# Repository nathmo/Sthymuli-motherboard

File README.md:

# Sthymuli-motherboard
This repo contains the PCB for the Sthymuli motherboard. Sthymuli is an educative robot aimed at children whith the aim of promoting collaborative learning.

The motherboard is designed arround a doughnut shape with addons that plug in the center. the shape was chosen to encourage equal access to up to four children at a time interracting with the device.

the circuit is splitted between one motherboard and three cardinalboard 
this repo has the motherboard

the cardinal board can be found there : https://github.com/nathmo/Sthymuli-cardinalboard

# Feature
The device contains the following sensors 

===

* # USB-C connector
* # Batterie + BMS
* # ESP32 + STM32
* # Speaker
* # Microphone
* # capacitive buttons (distributed arround the doughnut as discussed last time)
* # IR remote receive
* # 4 IR proximity Sensor
* # Motor Driver (so they can just connect the two wire of the motor and dont need to add a Hbridge on the dauther board
* # RGB LED (there I need to count how many and decide with you what we keep and what we breakout for the daugther board

# Daugther boards

the following will be available for the daugther board :

* IMU
* color sensor
* 2 DC motor channel
* LEDs
* IR proximity sensor / analog pin that can be used for sensing

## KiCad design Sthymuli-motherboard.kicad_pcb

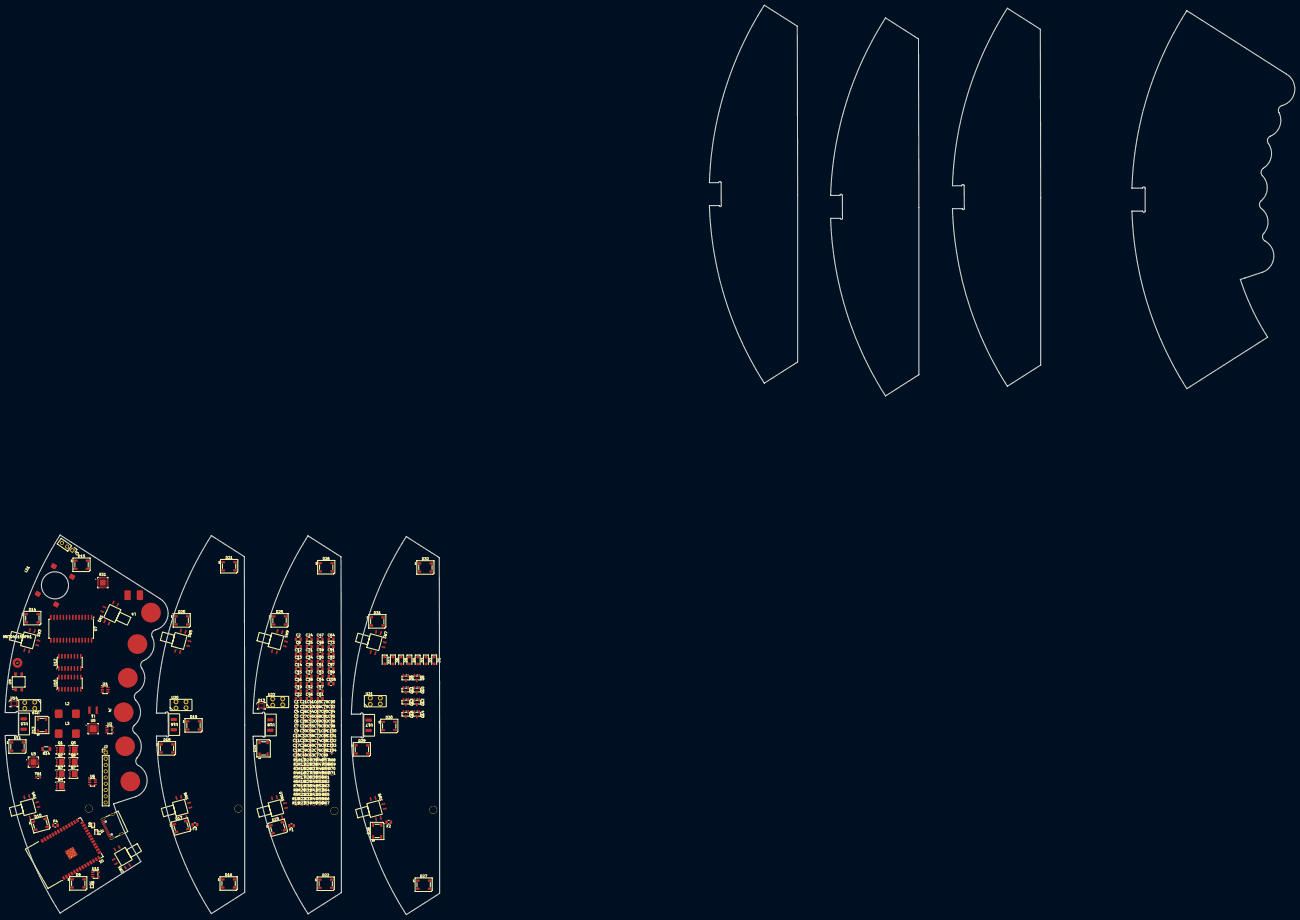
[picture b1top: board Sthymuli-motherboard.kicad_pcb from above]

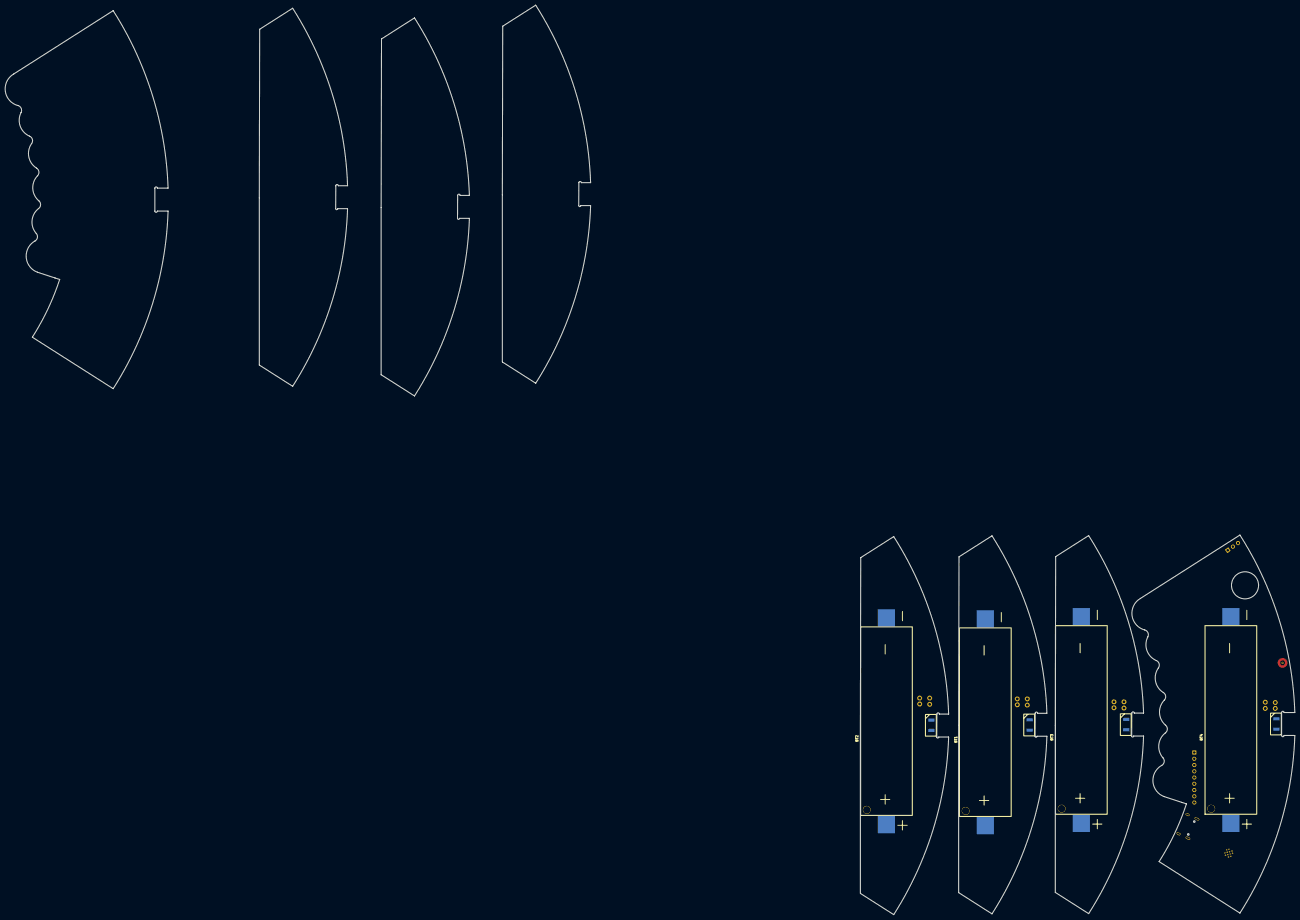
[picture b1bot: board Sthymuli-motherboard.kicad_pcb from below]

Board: 2 copper layers, 524.0 x 369.5 mm, 275 parts (4 on the bottom side), 189 nets, no tracks yet.

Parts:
BT1, BT2, BT3, BT4: Battery_Cell; Battery_Holder_18650_robop
C1, C10, C23, C32, C36, C43, C45, C55, C56, C62, C63, C65, C67, C68, C70, C71, C72, C74, C75, C76, C77, C78, C79, C80, C81, C82, C83, C84, C85, C86, C87, C88, C89, C90, C92, C94, C95, C96, C98, C100, C101, C102, C103, C104: 100nF; C_0402_1005Metric
C2: 22 uF; C_0805_2012Metric
C3, C4, C5, C6, C7: 220nF; C_0402_1005Metric
C8, C12, C13, C47, C48, C57, C61, C91, C93, C97, C99: 1uF; C_0805_2012Metric
C9, C11, C39, C40, C41, C44: 100pF; C_0402_1005Metric
C14, C15, C16, C19, C31, C34, C35, C64, C73, C105: 10uF; C_0805_2012Metric
C17: 1.8nF; C_0402_1005Metric
C18: 470nF; C_0402_1005Metric
C20: 33pF; C_0402_1005Metric
C21: 15pF; C_0402_1005Metric
C22: 680pF; C_0805_2012Metric
C24, C25: 33nF; C_0805_2012Metric
C26: 10nF; C_0402_1005Metric
C27, C28, C29: 10uF; C_0402_1005Metric
C30, C33: 47nF; C_0402_1005Metric
C37, C38, C46, C49: 22uF; C_0805_2012Metric
C42: 2.2uF; C_0805_2012Metric
C50, C54: 10nF; C_0805_2012Metric
C51: 1.5nF; C_0805_2012Metric
C52: 330pF; C_0402_1005Metric
C53: 4.7uF; C_0805_2012Metric
C58, C60: 1nF; C_0402_1005Metric
C59: 1uF; C_0402_1005Metric
C66, C69: 20pF; C_0402_1005Metric
D1, D2, D3, D4: D_Schottky; D_SOD-123F
D5, D6, D12: D; D_SOD-123F
D7, D8: LESD5D5.0C11G; D_SOD-523
D9, D10, D11, D13, D14, D15, D16, D17, D18, D19, D20, D21, D22, D23, D24, D25, D26, D27, D28, D29, D30, D31, D32: WS2812B; LED_WS2812B_PLCC4_5.0x5.0mm_P3.2mm
ES1: ES8374; QFN-28-1EP_4x4mm_P0.45mm_EP2.4x2.4mm
F1, F2, F3, F4: Fuse; R_0805_2012Metric
J1: USB_C_Receptacle_USB2.0_16P; USB_C_Receptacle_G-Switch_GT-USB-7010ASV
J2: Conn_01x09; PinHeader_1x09_P2.54mm_Vertical
J3: Conn_01x03; PinHeader_1x03_P2.54mm_Vertical
J4: Conn_01x06; ConnectorSpring
L1: 2.2uH; FHD4020S-2R2MT
L2, L3: 3.3uH; FXL0630-3R3-M
L4: L; TDK VFS5045VA301
LS1: Speaker; Speaker KELIKING KLJ-01304T-08R07W
MKTD4015BPN1: Microphone; SAMZO MIC-4013-G-G00
Q1, Q2, Q3, Q4, Q5, Q6: Q_NMOS_Depletion_GSD; VSON-8_3.3x3.3mm_P0.65mm_NexFET
Q7: PMOS; VSON-8_3.3x3.3mm_P0.65mm_NexFET
Q8, Q9, Q10, Q11, Q12, Q13, Q14, Q15: NX7002AK; SOT-23
R1, R2, R3, R4, R6, R9, R15, R36, R37: 10R; C_0201_0603Metric
R5, R7: 5K1; C_0201_0603Metric
R8, R13, R16, R48, R59, R69, R70: 100R; C_0201_0603Metric
R10, R12: OL; C_0201_0603Metric
R11, R68: 0R; C_0201_0603Metric
R14: 0.001 R; R_1206_3216Metric
R17: 100K; C_0201_0603Metric
R18: 300K; C_0201_0603Metric
R19, R26: 10M; C_0201_0603Metric
R20: 470K; C_0201_0603Metric
R21: 270K; C_0201_0603Metric
R22, R23, R49, R58: 2K2; C_0201_0603Metric
R24, R28: 5k1; C_0201_0603Metric
R25: 40.2K; C_0201_0603Metric
R27: 1R; C_0201_0603Metric
R29, R31: 4.99R; C_0201_0603Metric
R30, R43: 0.01 R; C_0201_0603Metric
R32, R33, R34, R42, R45, R46, R47, R71: 10K; C_0201_0603Metric
R35: 30K; C_0201_0603Metric
R38: 47K; C_0201_0603Metric
R39: 15K; C_0201_0603Metric
R40: 137K; C_0201_0603Metric
R41: 53.6K; C_0201_0603Metric
R44: 1K; C_0201_0603Metric
R50, R51, R52, R53, R54, R55, R56, R57: 3K3; C_0201_0603Metric
R60, R61, R62, R63, R64, R65, R66, R67: 27R; C_0201_0603Metric
SW1, SW2, SW3, SW4, SW5, SW6, SW7, SW8, SW9, SW10: SW_Push; XKB5858
TH1: Thermistor; R_0603_1608Metric
U1: ESP32-S3-WROOM-1
U2: AP2112K-3.3; SOT-23-5
U3: BQ76905RGRR; Texas_RGP0020H_VQFN-20-1EP_4x4mm_P0.5mm_EP2.4x2.4mm
U4, U6: AP62300WU; TSOT-23-6
U5: BQ25713; QFN-32-1EP_4x4mm_P0.4mm_EP2.9x2.9mm
U7: MCP23017_SO; SOIC-28W_7.5x17.9mm_P1.27mm
U8: AP22913CN4; WLCSP-4_0.89x0.89mm_Layout2x2_P0.5mm
U9: IRM-H6xxT; Everlight_IRM-H6xxT
U10, U12: 74HC4051; SOIC-16_3.9x9.9mm_P1.27mm
U11: MCP6L01x-xOT; SOT-23-5
U13, U14: LSM6DS3; LGA-14_3x2.5mm_P0.5mm_LayoutBorder3x4y
U15, U16, U17, U18: ITR9909; ITR_9909_Horizontal
U19, U20, U21, U22: ITR9909; ITR_9909_Vertical

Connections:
+3V3: C47.2, C50.2, C54.2, C55.1, C56.1, C64.1, C67.1, C103.2, C105.2, ES1.5 (PVDD), ES1.6 (DVDD), ES1.16 (AVDD), J2.1, L4.1, R22.2, R23.2, R33.2, R34.1, R45.1, R48.2, R50.1, R51.1, R52.1, R53.1, R54.1, R55.1, R56.1, R57.1, R60.2, R61.2, R62.2, R63.2, R64.2, R65.2, R66.2, R67.2, R71.2, U2.5 (VOUT), U7.9 (VDD), U7.18 (~RESET), U8.A1 (OUT), U10.16 (VCC), U11.5 (V+), U12.16 (VCC), U13.1 (SDO/SA0), U13.5 (VDDIO), U13.8 (VDD), U13.12 (CS), U14.5 (VDDIO), U14.8 (VDD), U14.12 (CS)
+5V: C44.2, C46.2, C49.2, C62.1, C63.1, C68.1, C70.1, C71.1, C72.1, C74.1, C76.1, C77.1, C78.1, C79.1, C80.1, C81.1, C82.1, C83.1, C84.1, C85.1, C86.1, C87.1, C88.1, C89.1, C90.1, C92.1, C94.1, C95.1, C96.1, C98.1, C100.1, C101.1, C102.1, C104.1, D9.1 (VDD), D10.1 (VDD), D11.1 (VDD), D12.2 (A), D14.1 (VDD), D15.1 (VDD), D16.1 (VDD), D17.1 (VDD), D18.1 (VDD), D19.1 (VDD), D20.1 (VDD), D21.1 (VDD), D22.1 (VDD), D23.1 (VDD), D24.1 (VDD), D25.1 (VDD), D26.1 (VDD), D27.1 (VDD), D28.1 (VDD), D29.1 (VDD), D30.1 (VDD), D31.1 (VDD), D32.1 (VDD), J4.1, L3.2, R10.1, R41.1
+BATT: BT1.1 (+), C45.1, D5.2 (A), D6.2 (A), F1.1, R1.1, R37.1, R43.2
/D+: D8.1 (K), J1.A6 (D+), J1.B6 (D+), U1.14 (USB_D+)
/D-: D7.1 (K), J1.A7 (D-), J1.B7 (D-), U1.13 (USB_D-)
/MICBIAS: C99.1, ES1.21 (MICBIAS), R59.2
/MIC_N: C59.1, ES1.23 (LIN2)
/MIC_P: C57.1, ES1.22 (RIN2)
ACC_A_INT1: U1.11 (IO18), U14.4 (INT1)
ACC_B_INT1: U1.10 (IO17), U13.4 (INT1)
BMS_ALERT: U1.15 (IO3), U3.14 (ALERT)
BOOT_MODE: C32.1, SW2.2, U1.27 (IO0)
CHRG_OK: R34.2, U5.4 (CHRG_OK), U7.24 (GPA3)
EXT_GPIO_1: J4.4, U1.7 (IO7)
EXT_GPIO_2: J4.5, U1.12 (IO8)
GND: C1.2, C2.2, C4.1, C7.1, C8.2, C11.2, C12.2, C13.2, C14.2, C15.2, C16.2, C17.2, C18.2, C19.2, C20.2, C21.2, C22.2, C23.2, C24.2, C25.2, C26.2, C27.2, C28.2, C29.2, C31.2, C32.2, C34.2, C35.2, C37.1, C38.1, C40.2, C41.2, C42.1, C46.1, C47.1, C48.1, C49.1, C50.1, C53.2, C54.1, C55.2, C56.2, C58.2, C60.2, C61.2, C62.2, C63.2, C65.2, C66.2, C68.2, C69.2, C70.2, C71.2, C72.2, C74.2, C76.2, C77.2, C78.2, C79.2, C80.2, C81.2, C82.2, C83.2, C84.2, C85.2, C86.2, C87.2, C88.2, C89.2, C90.2, C92.2, C94.2, C95.2, C96.2, C98.2, C100.2, C101.2, C102.2, C104.2, D7.2 (A), D8.2 (A), D9.3 (VSS), D10.3 (VSS), D11.3 (VSS), D13.3 (VSS), D14.3 (VSS), D15.3 (VSS), D16.3 (VSS), D17.3 (VSS), D18.3 (VSS), D19.3 (VSS), D20.3 (VSS), D21.3 (VSS), D22.3 (VSS), D23.3 (VSS), D24.3 (VSS), D25.3 (VSS), D26.3 (VSS), D27.3 (VSS), D28.3 (VSS), D29.3 (VSS), D30.3 (VSS), D31.3 (VSS), D32.3 (VSS), J1.A1 (GND), J1.A12 (GND), J1.B1 (GND), J1.B12 (GND), J1.S1 (SHIELD), J2.9, J4.6, Q2.2 (S), Q4.2 (S), Q5.2 (S), Q8.2 (S), Q9.2 (S), Q10.2 (S), Q11.2 (S), Q12.2 (S), Q13.2 (S), Q14.2 (S), Q15.2 (S), R5.1, R7.1, R18.2, R21.2, R26.2, R35.2, R39.2, R40.2, R42.2, R46.2, R49.1, R68.1, SW1.1, SW2.1, SW3.2, SW4.2, SW5.2, SW6.2, SW7.2, SW8.2, SW9.2, SW10.2, TH1.2, U1.1 (GND), U1.40 (GND), U1.41 (GND), U2.2 (GND), U3.11 (VSS), U3.21 (EXP), U4.1 (GND), U5.27 (PGND), U6.1 (GND), U7.10 (VSS), U7.15 (A0), U7.16 (A1), U7.17 (A2), U8.B1 (GND), U9.1 (GND), U9.2 (GND), U10.6 (~E), U10.7 (VEE), U10.8 (GND), U11.2 (V-), U12.6 (~E), U12.7 (VEE), U12.8 (GND), U13.2 (SDX), U13.3 (SCX), U13.6 (GND), U13.7 (GND), U14.1 (SDO/SA0), U14.2 (SDX), U14.3 (SCX), U14.6 (GND), U14.7 (GND), U15.3, U16.3, U17.3, U18.3, U19.3, U20.3, U21.3, U22.3
GNDA: C64.2, C67.2, C73.2, C75.2, C91.2, C93.2, C97.2, C99.2, C103.1, C105.1, ES1.3 (DGND), ES1.12 (SPKGND), ES1.17 (AGND), ES1.29 (PGND), R68.2
GPIO_INTA: U1.38 (IO2), U7.20 (INTA)
GPIO_INTB: U1.39 (IO1), U7.19 (INTB)
I2S_DOUT: ES1.8 (ASDOUT), U1.8 (IO15)
I2S_DSIN: ES1.10 (ASDIN), U1.22 (IO14)
I2S_LCLK: ES1.9 (DLRCK), U1.21 (IO13)
I2S_MCLK: ES1.2 (MCLK), U1.9 (IO16)
I2S_SCLK: ES1.7 (BCLK), U1.20 (IO12)
INT_WS2812_DIN: D13.4 (DIN), U1.17 (IO9)
IR_MODULATION: U1.18 (IO10), U12.3 (A)
IR_REC_0: R50.2, U10.13 (A0), U15.4
IR_REC_1: R51.2, U10.14 (A1), U16.4
IR_REC_2: R52.2, U10.15 (A2), U17.4
IR_REC_3: R53.2, U10.12 (A3), U18.4
IR_REC_4: R54.2, U10.1 (A4), U19.4
IR_REC_5: R55.2, U10.5 (A5), U20.4
IR_REC_6: R56.2, U10.2 (A6), U21.4
IR_REC_7: R57.2, U10.4 (A7), U22.4
IR_S0: U7.26 (GPA5), U10.11 (S0), U12.11 (S0)
IR_S1: U7.27 (GPA6), U10.10 (S1), U12.10 (S1)
IR_S2: U7.28 (GPA7), U10.9 (S2), U12.9 (S2)
IR_TRA_0: Q8.1 (G), U12.13 (A0)
IR_TRA_1: Q9.1 (G), U12.14 (A1)
IR_TRA_2: Q10.1 (G), U12.15 (A2)
IR_TRA_3: Q11.1 (G), U12.12 (A3)
IR_TRA_4: Q12.1 (G), U12.1 (A4)
IR_TRA_5: Q13.1 (G), U12.5 (A5)
IR_TRA_6: Q14.1 (G), U12.2 (A6)
IR_TRA_7: Q15.1 (G), U12.4 (A7)
IR_analog: C52.1, R47.1, U1.4 (IO4), U11.1
IR_receiver: U1.19 (IO11), U9.3 (OUT)
unnamed: BT1.2 (-), BT2.1 (+), D1.2 (A), F2.1, R2.1
unnamed: BT2.2 (-), BT3.1 (+), D2.2 (A), F3.1, R3.1
unnamed: BT3.2 (-), BT4.1 (+), D3.2 (A), F4.1, R4.1
unnamed: BT4.2 (-), D4.2 (A), R6.1, R13.2, R14.2
unnamed: C14.1, C15.1, C16.1, C19.1, R11.1, R27.2, R29.2, R30.2
unnamed: C17.1, R25.2
unnamed: C22.1, R32.2
unnamed: C51.2, R44.1
unnamed: C61.1, R58.1, R59.1
unnamed: D1.1 (K), F1.2
unnamed: D2.1 (K), F2.2
unnamed: D3.1 (K), F3.2
unnamed: D4.1 (K), F4.2
unnamed: D5.1 (K), R8.1
unnamed: D6.1 (K), R9.1
unnamed: D10.2 (DOUT), D15.4 (DIN)
unnamed: D11.2 (DOUT), D16.4 (DIN)
unnamed: C65.1, D12.1 (K), D13.1 (VDD)
unnamed: D13.2 (DOUT), D17.4 (DIN)
unnamed: D9.2 (DOUT), D14.4 (DIN)
unnamed: D14.2 (DOUT), D18.4 (DIN)
unnamed: D15.2 (DOUT), D19.4 (DIN)
unnamed: D16.2 (DOUT), D20.4 (DIN)
unnamed: D17.2 (DOUT), D21.4 (DIN)
unnamed: D18.2 (DOUT), D22.4 (DIN)
unnamed: D19.2 (DOUT), D23.4 (DIN)
unnamed: D20.2 (DOUT), D24.4 (DIN)
unnamed: D21.2 (DOUT), D25.4 (DIN)
unnamed: D22.2 (DOUT), D26.4 (DIN)
unnamed: D23.2 (DOUT), D27.4 (DIN)
unnamed: D24.2 (DOUT), D28.4 (DIN)
unnamed: D25.2 (DOUT), D29.4 (DIN)
unnamed: D26.2 (DOUT), D30.4 (DIN)
unnamed: D27.2 (DOUT), D31.4 (DIN)
unnamed: D28.2 (DOUT), D32.4 (DIN)
unnamed: C93.1, ES1.19 (ADC/REF)
unnamed: C66.1, ES1.1 (CCLK), R70.2
unnamed: C69.1, ES1.28 (CDATA), R69.2
unnamed: ES1.27 (CE), R71.1
unnamed: C91.1, ES1.18 (DAC/REF)
unnamed: ES1.11 (SPKLN), LS1.2
unnamed: ES1.14 (SPKLP), LS1.1
unnamed: C73.1, C75.1, ES1.13 (SPKVDD), L4.2
unnamed: C97.1, ES1.20 (VMID)
unnamed: J1.A5 (CC1), R7.2
unnamed: J1.B5 (CC2), R5.2
unnamed: J2.2, U1.37 (TXD0)
unnamed: J2.3, U1.36 (RXD0)
unnamed: J2.4, U1.31 (IO38)
unnamed: J2.5, U1.32 (IO39)
unnamed: J2.6, U1.33 (IO40)
unnamed: J2.7, U1.34 (IO41)
unnamed: J2.8, U1.35 (IO42)
unnamed: J3.1, U7.21 (GPA0)
unnamed: J3.2, U7.22 (GPA1)
unnamed: J3.3, U7.23 (GPA2)
unnamed: C57.2, C58.1, MKTD4015BPN1.2 (+), R49.2
unnamed: C59.2, C60.1, MKTD4015BPN1.1 (-), R58.2
unnamed: Q1.3 (D), Q2.3 (D)
unnamed: Q1.1 (G), R19.1, R24.1
unnamed: Q1.2 (S), R14.1, R16.1, R19.2
unnamed: Q2.1 (G), R26.1, R28.1
unnamed: C26.1, Q3.3 (D), R30.1, R31.2
unnamed: Q3.1 (G), U5.31 (HIDRV1)
unnamed: C30.1, L1.1, Q3.2 (S), Q4.3 (D), U5.32 (SW1)
unnamed: Q4.1 (G), U5.29 (LODRV1)
unnamed: C33.1, L1.2, Q5.3 (D), Q6.2 (S), U5.23 (SW2)
unnamed: Q5.1 (G), U5.26 (LODRV2)
unnamed: C27.1, C28.1, C29.1, C31.1, C34.1, C35.1, Q6.3 (D), Q7.3 (S), U4.3 (IN), U5.22 (VSYS), U6.3 (IN)
unnamed: Q6.1 (G), U5.24 (HIDRV2)
unnamed: C45.2, C48.2, Q7.1 (D), R36.1, R43.1
unnamed: Q7.2 (G), U5.21 (~BATDRV)
unnamed: Q8.3 (D), U15.1
unnamed: Q9.3 (D), U16.1
unnamed: Q10.3 (D), U17.1
unnamed: Q11.3 (D), U18.1
unnamed: Q12.3 (D), U19.1
unnamed: Q13.3 (D), U20.1
unnamed: Q14.3 (D), U21.1
unnamed: Q15.3 (D), U22.1
unnamed: R60.1, U15.2
unnamed: R61.1, U16.2
unnamed: R62.1, U17.2
unnamed: R63.1, U18.2
unnamed: R64.1, U19.2
unnamed: R65.1, U20.2
unnamed: R66.1, U21.2
unnamed: R67.1, U22.2
unnamed: C1.1, C2.1, C37.2, C38.2, C39.2, L2.2, R38.1, U1.2 (3V3), U8.A2 (IN)
unnamed: R12.2, U2.1 (VIN), U2.3 (EN)
unnamed: C11.1, C13.1, R8.2, U3.17 (BAT)
unnamed: R28.2, U3.10 (CHG)
unnamed: R24.2, U3.9 (DSG)
unnamed: C8.1, R9.2, U3.16 (REGSRC)
unnamed: C9.2, C10.2, R16.2, U3.7 (SRN)
unnamed: C9.1, C10.1, R13.1, U3.6 (SRP)
unnamed: TH1.1, U3.8 (TS)
unnamed: C7.2, R6.2, U3.5 (VC0)
unnamed: C3.1, C4.2, R4.2, U3.4 (VC1)
unnamed: C3.2, C6.1, R3.2, U3.1 (VC3A), U3.2 (VC3B), U3.3 (VC2)
unnamed: C5.1, C6.2, R2.2, U3.19 (VC4A), U3.20 (VC4B)
unnamed: C5.2, R1.2, U3.18 (VC5)
unnamed: C36.1, U4.6 (BST)
unnamed: C39.1, R38.2, R39.1, U4.4 (FB)
unnamed: C36.2, L2.1, U4.2 (SW)
unnamed: C25.1, R31.1, U5.2 (ACN)
unnamed: C24.1, R29.1, U5.3 (ACP)
unnamed: C30.2, U5.30 (BTST1)
unnamed: C33.2, U5.25 (BTST2)
unnamed: R17.2, R18.1, U5.18 (CELL_BATPRESZ)
unnamed: C20.1, R25.1, U5.16 (COMP1)
unnamed: C21.1, R32.1, U5.17 (COMP2)
unnamed: C41.1, R40.1, U5.8 (IADPT)
unnamed: C40.1, U5.9 (IBAT)
unnamed: R20.2, R21.1, U5.6 (ILIM_HIZ)
unnamed: R35.1, U5.10 (PSYS)
unnamed: C42.2, R15.1, U5.28 (REGN)
unnamed: R37.2, U5.19 (SRN)
unnamed: R36.2, U5.20 (SRP)
unnamed: C18.1, R27.1, U5.1 (VBUS)
unnamed: C12.1, R15.2, R17.1, R20.1, U5.7 (VDDA)
unnamed: C43.1, U6.6 (BST)
unnamed: C44.1, R41.2, R42.1, U6.4 (FB)
unnamed: C43.2, L3.1, U6.2 (SW)
unnamed: C53.1, R48.1, U9.4 (Vcc)
unnamed: R44.2, U10.3 (A)
unnamed: R45.2, R46.1, U11.3 (+)
unnamed: C51.1, C52.2, R47.2, U11.4 (-)
OTG: U5.5 (OTG/VAP), U7.25 (GPA4)
PWR_ON: U1.6 (IO6), U6.5 (EN), U8.B2 (ON)
RST: C23.1, R33.1, SW1.2, U1.3 (EN)
SCL: J4.3, R22.1, R70.1, U1.24 (IO47), U3.12 (SCL), U5.13 (SCL), U7.12 (SCK), U13.13 (SCL), U14.13 (SCL)
SDA: J4.2, R23.1, R69.1, U1.25 (IO48), U3.13 (SDA), U5.12 (SDA), U7.13 (SDA), U13.14 (SDA), U14.14 (SDA)
VBUS: J1.A4 (VBUS), J1.A9 (VBUS), J1.B4 (VBUS), J1.B9 (VBUS), R10.2, R11.2, R12.1
btn_EAST_DOWN: SW8.1, U7.6 (GPB5)
btn_EAST_UP: SW7.1, U7.5 (GPB4)
btn_NORTH_DOWN: SW4.1, U7.2 (GPB1)
btn_NORTH_UP: SW3.1, U7.1 (GPB0)
btn_SOUTH_DOWN: SW6.1, U7.4 (GPB3)
btn_SOUTH_UP: SW5.1, U7.3 (GPB2)
btn_WEST_DOWN: SW10.1, U7.8 (GPB7)
btn_WEST_UP: SW9.1, U7.7 (GPB6)

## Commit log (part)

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2025-11-26 added empty project
2025-11-26 added license
2025-11-27 added enclosure sketch + readme + blocks of schematic
2025-12-19 added power switch + reflexion
2025-12-21 Tried to implement fast charging with USB-C PD
    likely not going to happen do to being far from trivial to implement right... I might revert to a simpler charger
2026-01-08 reimplementing the charging circuit using a known working one
2026-01-11 implemented new charging circuit, added USB serial
2026-01-11 Auto-export KiCad PDFs
2026-01-12 implemented part of audio + accel
2026-01-27 almost done. only the proximity sensor left to do
2026-02-04 schematic done
2026-02-05 making the part list / BOM
    currently 20-30 CHF per PCB (component wise)
2026-02-19 upgrading ESP+ battery
2026-02-19 upgraded to ESP32-S3, working on new power stage
2026-03-01 switched to LiFe, redisigned power stage
    4S lifepack
    Fastcharge
    non latching button for pwr on/off
    OTG for back powering device
    3A 5V and 3A 3v3 available for the board
2026-03-12 added BOM
2026-03-12 added footprint
2026-03-17 started layout of component
2026-03-17 closing edgecut
2026-03-25 fixed some footprint issue, advanced layout
2026-03-26 progress on layout
2026-03-31 starting from scratch the routing. autorouter was not good
2026-04-01 280 left to route, power mostly done
2026-04-01 removed lock
2026-04-02 64 left to route
2026-04-02 done routing
2026-04-03 cleaning board
2026-04-04 done routing + cleaning PCB
2026-04-04 regenerated output
2026-04-04 added fabrication file
2026-04-04 Enhance README with additional details and images
    Updated README.md to improve formatting and add information about the cardinal board.
2026-04-09 slowly re routing the broken track
    fixed resistor footprint
    updated DRC checks
    improved schematic readability
2026-04-09 40 left
2026-04-10 regenerated file + BOM
2026-04-10 removed kicad bck
2026-04-10 regenerated the file before placing the order
2026-04-10 removed all file that are obselete
2026-04-10 removed obselete file
2026-04-10 updated bom for BOTH side
2026-04-10 updated header name of POS file
2026-04-10 removed non populated component
2026-04-17 added step
